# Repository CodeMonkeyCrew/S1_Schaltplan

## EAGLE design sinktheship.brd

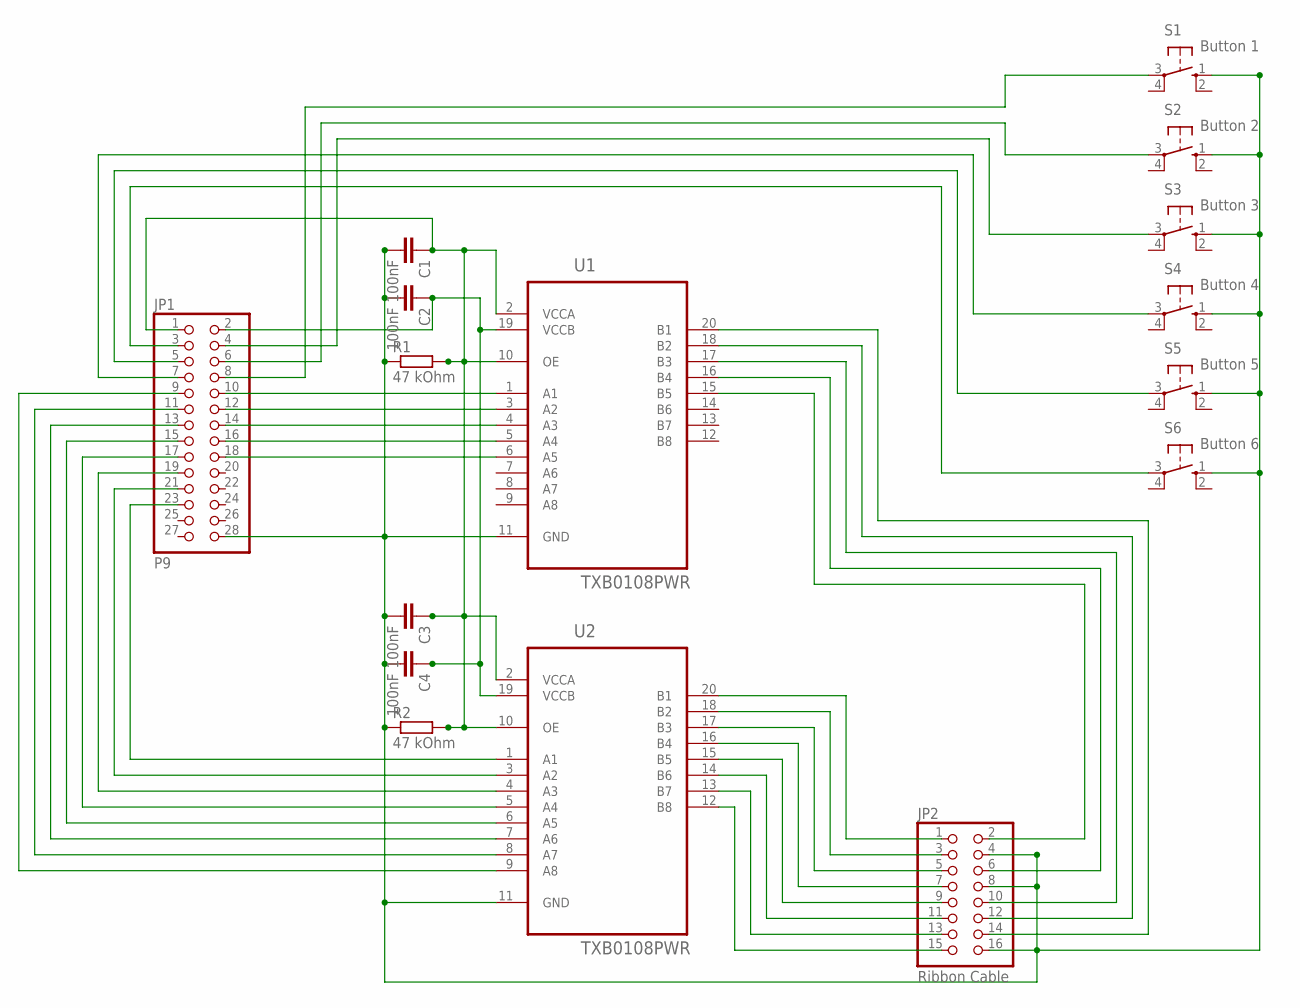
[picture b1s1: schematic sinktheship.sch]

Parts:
C1, C2, C3, C4: 100nF; C0603
JP1: P9; 2X14
JP2: Ribbon Cable; 2X08
R1, R2: 47 kOhm; R0603
S1: Button 1; B3F-10XX
S2: Button 2; B3F-10XX
S3: Button 3; B3F-10XX
S4: Button 4; B3F-10XX
S5: Button 5; B3F-10XX
S6: Button 6; B3F-10XX
U1, U2: TXB0108PWR; SOP65P640X120-20N

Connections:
unnamed: JP1.16, U1.5 (A4)
unnamed: JP2.15, U2.12 (B8)
unnamed: JP1.4, S3.3
unnamed: JP2.13, U2.13 (B7)
unnamed: JP1.10, U1.1 (A1)
unnamed: JP1.3, S6.3
unnamed: JP1.12, U1.3 (A2)
unnamed: JP1.18, U1.6 (A5)
unnamed: JP1.5, S5.3
unnamed: JP1.7, S4.3
unnamed: JP1.9, U2.9 (A8)
unnamed: JP1.14, U1.4 (A3)
unnamed: JP1.23, U2.1 (A1)
unnamed: JP1.21, U2.3 (A2)
unnamed: JP1.19, U2.4 (A3)
unnamed: JP1.17, U2.5 (A4)
unnamed: JP1.15, U2.6 (A5)
unnamed: JP1.13, U2.7 (A6)
unnamed: JP1.11, U2.8 (A7)
unnamed: JP2.11, U2.14 (B6)
unnamed: C1.2, C2.2, C3.2, C4.2, JP1.28, JP2.4, JP2.8, JP2.16, R1.1, R2.1, S1.1 (S), S2.1 (S), S3.1 (S), S4.1 (S), S5.1 (S), S6.1 (S), U1.11 (GND), U2.11 (GND)
unnamed: JP2.9, U2.15 (B5)
unnamed: JP2.7, U2.16 (B4)
unnamed: JP2.5, U2.17 (B3)
unnamed: JP2.3, U2.18 (B2)
unnamed: JP2.1, U2.20 (B1)
unnamed: JP2.14, U1.20 (B1)
unnamed: JP2.12, U1.18 (B2)
unnamed: JP2.10, U1.17 (B3)
unnamed: JP2.6, U1.16 (B4)
unnamed: JP2.2, U1.15 (B5)
unnamed: JP1.6, S2.3
unnamed: JP1.8, S1.3
VCCA: C1.1, C3.1, JP1.1, R1.2, R2.2, U1.2 (VCCA), U1.10 (OE), U2.2 (VCCA), U2.10 (OE)
VCCB: C2.1, C4.1, JP1.2, U1.19 (VCCB), U2.19 (VCCB)

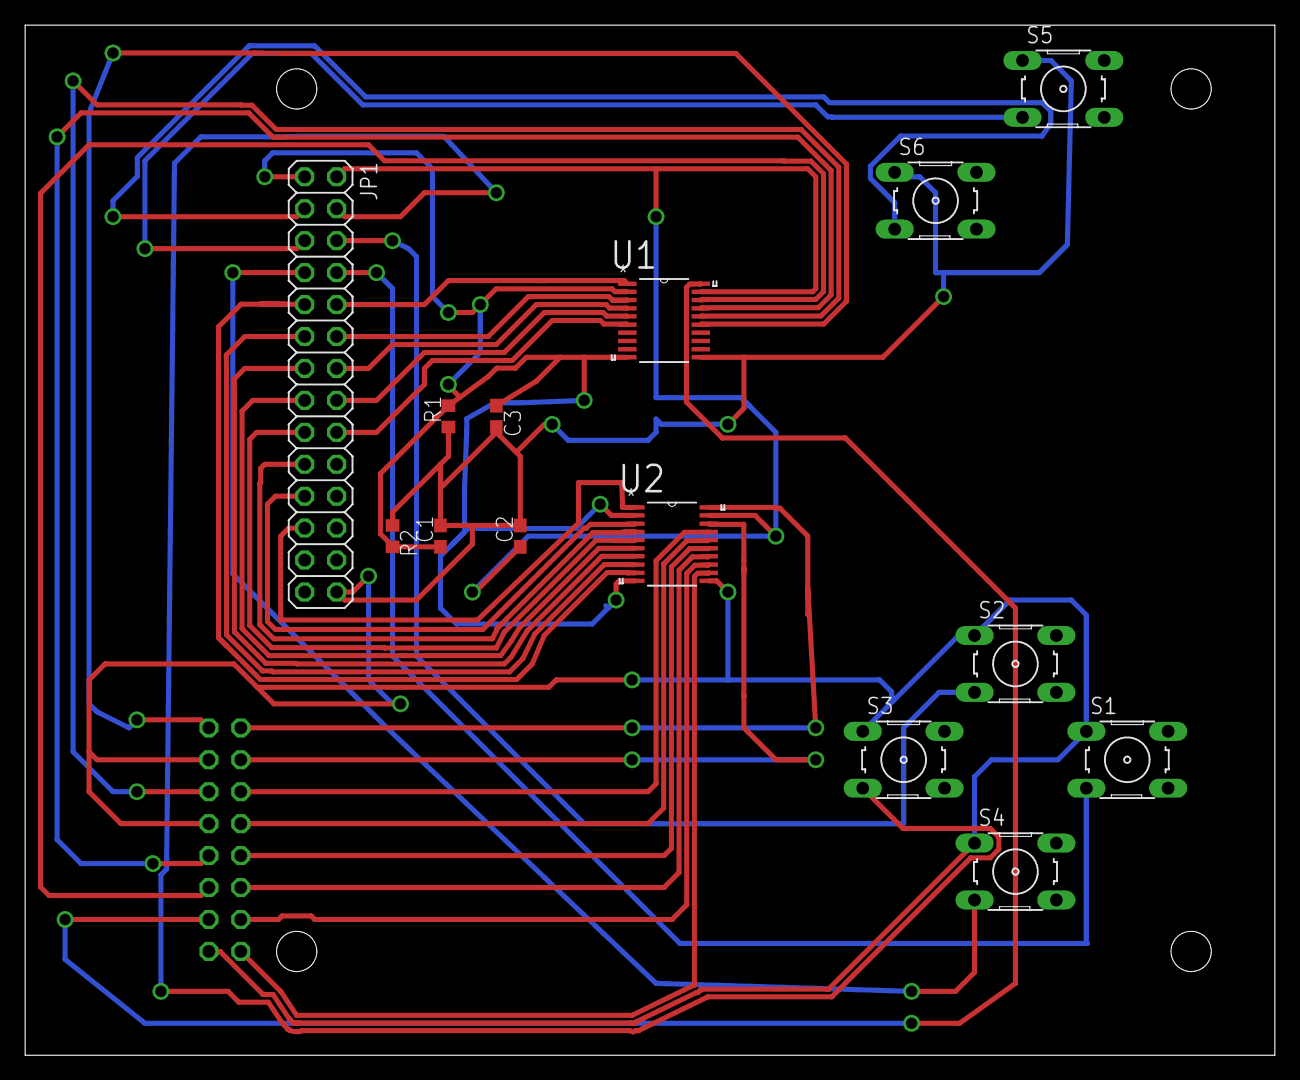
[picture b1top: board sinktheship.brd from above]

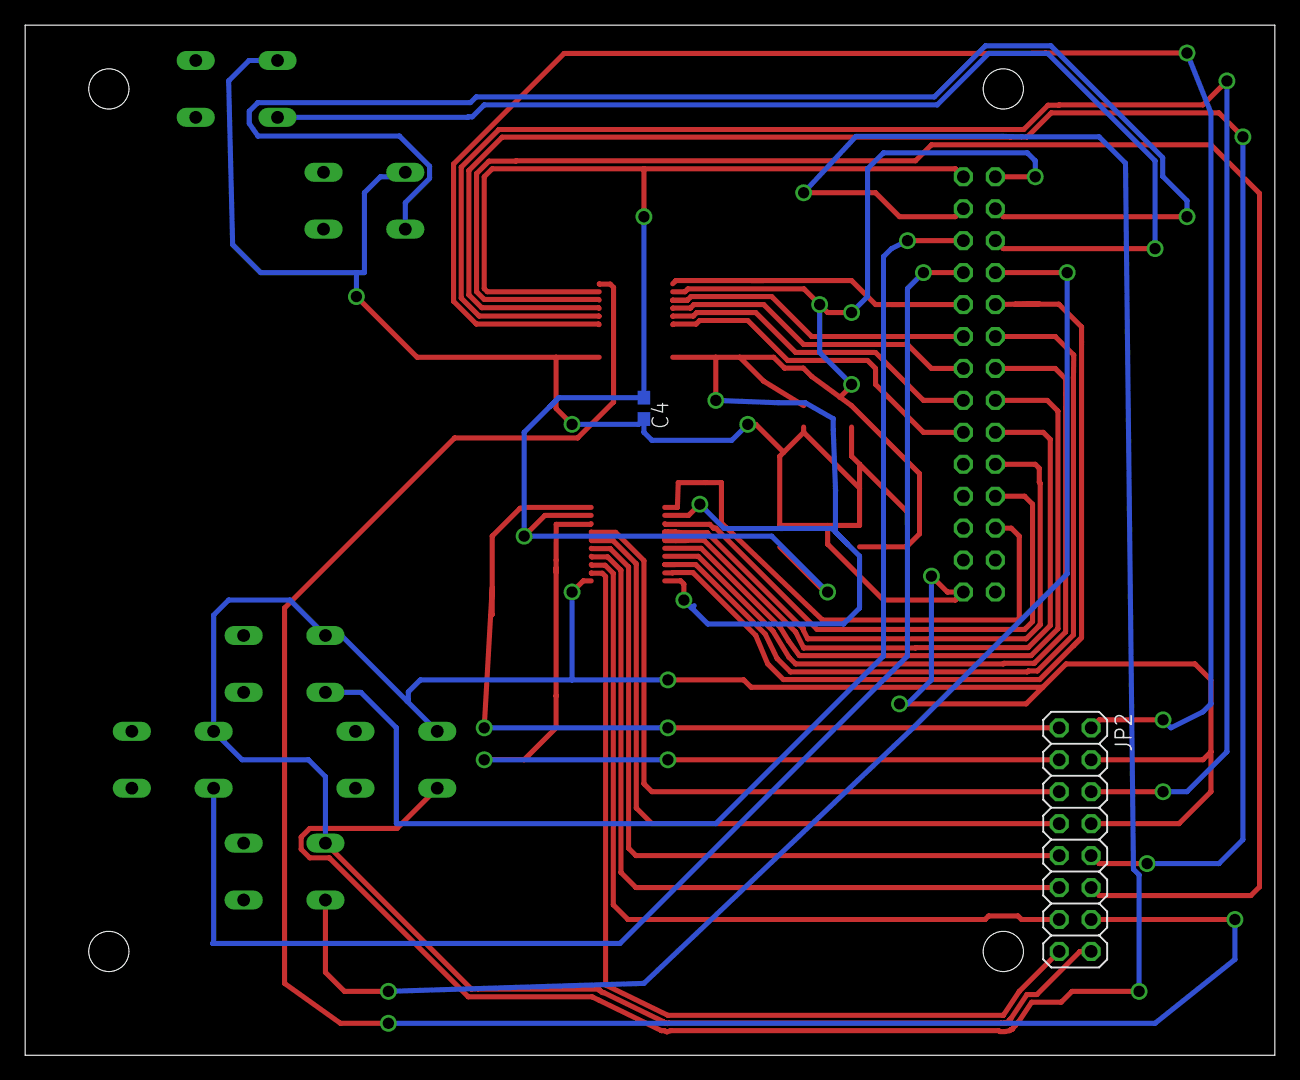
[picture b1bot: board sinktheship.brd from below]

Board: 2 copper layers, 99.4 x 81.9 mm, 16 parts (2 on the bottom side), 35 nets.

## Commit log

2017-05-06 init commit
2017-05-06 schaltplan pdf added
2017-05-12 add pcb schematic and board layout
2017-05-18 rework done
